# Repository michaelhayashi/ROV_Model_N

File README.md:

ROV_Model_N
===========

Purdue IEEE ROV Team project files

All of the electrical and code files are provided here free of charge for enthusiasts to modify, hack, fix, and do whatever to under OSHW. All files are given without any guarantee.

If anyone does have a cool idea about how to reuse/repurpose any of this hardware, or notices any glaring issues with it, let us know at purduerov@gmail.com

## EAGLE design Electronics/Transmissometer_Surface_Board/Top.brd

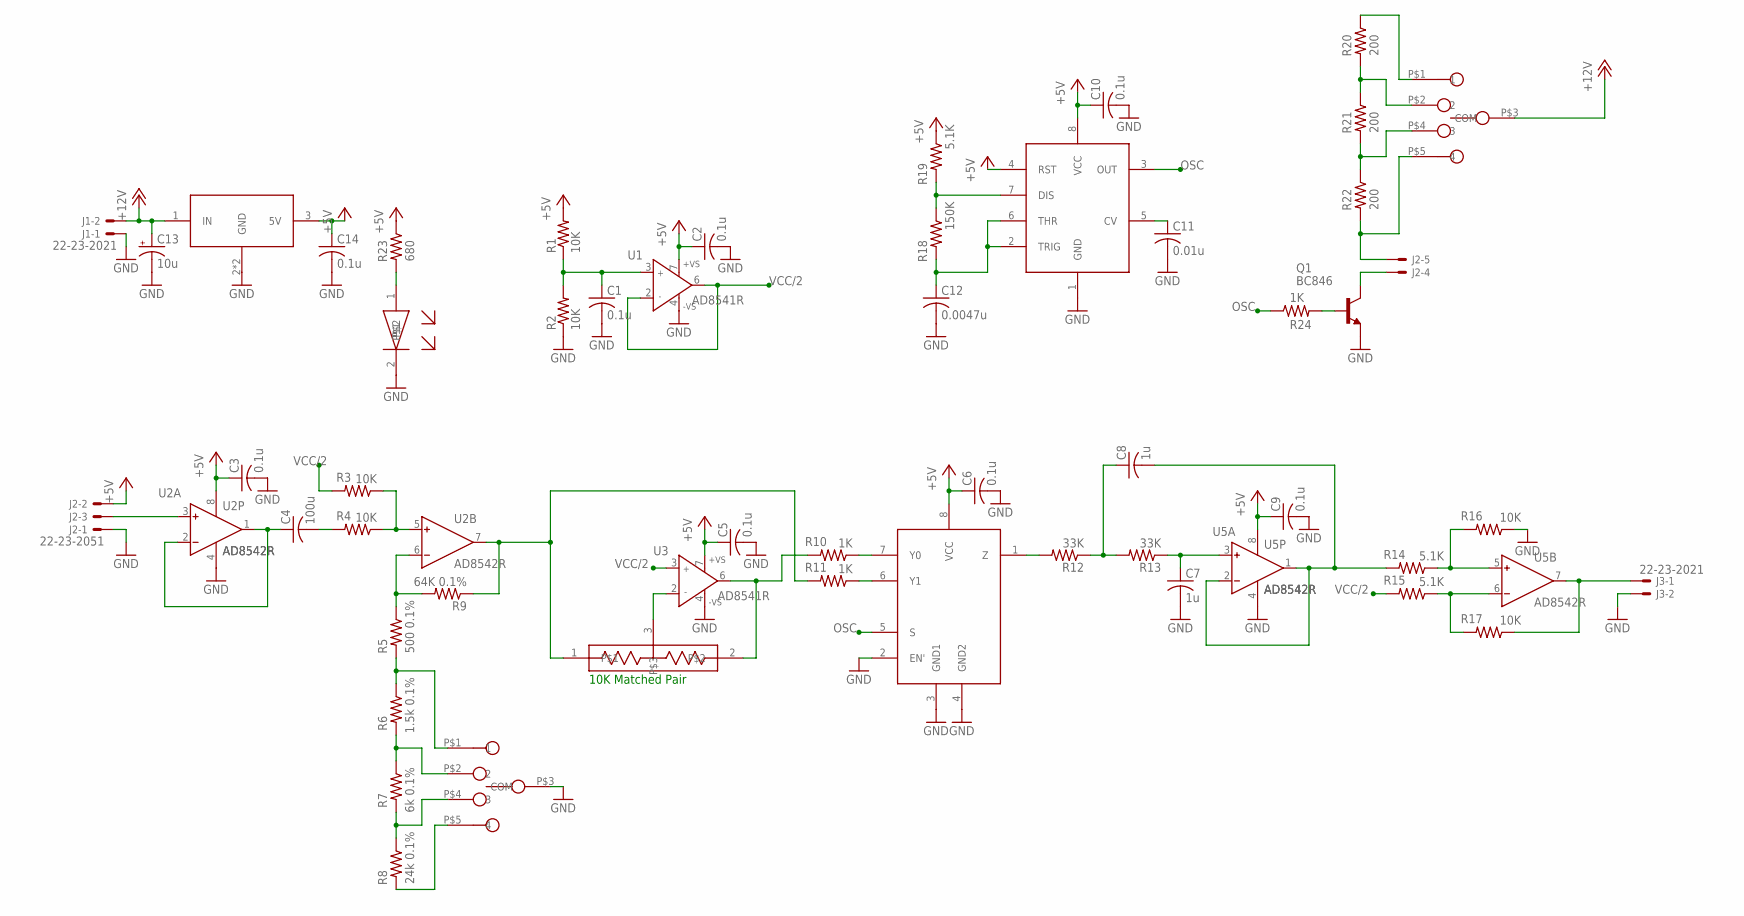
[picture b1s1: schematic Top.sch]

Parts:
C1, C2, C3, C5, C6, C9, C10, C14: 0.1u; C0805
C4: 100u; C1206
C7, C8: 1u; C0805
C11: 0.01u; C0805
C12: 0.0047u; C0805
C13: 10u; E2-5
D1: LGN971; R1206
J1, J3: 22-23-2021
J2: 22-23-2051
Q1: BC846; SOT23
R1, R2, R3, R4, R16, R17: 10K; R0805
R5: 500 0.1%; R0805
R6: 1.5k 0.1%; R0805
R7: 6k 0.1%; R0805
R8: 24k 0.1%; R0805
R9: 64K 0.1%; R0805
R10, R11, R24: 1K; R0805
R12, R13: 33K; R0805
R14, R15, R19: 5.1K; R0805
R18: 150K; R0805
R20, R21, R22: 200; R0805
R23: 680; R0805
RN1: MPMT2002; SOT23
SW1, SW2: STS1400; 2-3SW
U1, U3: AD8541R; SO8
U2, U5: AD8542R; SO8
U4: 74LVC1G53; SOP08
U6: NA555; SO8
U7: UA78M05CDCYR; SOT223-W

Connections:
+5V: C2.1, C3.1, C5.1, C6.1, C9.1, C10.1, C14.1, J2.2, R1.2, R19.1, R23.1, U1.7 (+VS), U2.8 (V+), U3.7 (+VS), U4.8 (VCC), U5.8 (V+), U6.4 (RST), U6.8 (VCC), U7.3 (5V)
+12V: C13.+, J1.2, SW2.P$3 (COM), U7.1 (IN)
GND: C1.2, C2.2, C3.2, C5.2, C6.2, C7.2, C9.2, C10.2, C11.2, C12.2, C13.-, C14.2, D1.2, J1.1, J2.1, J3.2, Q1.2 (E), R2.1, R16.1, SW1.P$3 (COM), U1.4 (-VS), U2.4 (V-), U3.4 (-VS), U4.2 (EN'), U4.3 (GND1), U4.4 (GND2), U5.4 (V-), U6.1 (GND), U7.2 (GND), U7.4 (GND)
unnamed: C1.1, R1.1, R2.2, U1.3 (IN+)
unnamed: C4.1, U2.1 (OUT), U2.2 (IN-)
unnamed: C4.2, R4.2
unnamed: R3.1, R4.1, U2.5 (IN+)
unnamed: R5.1, R9.2, U2.6 (IN-)
unnamed: R9.1, R11.2, RN1.1, U2.7 (OUT)
unnamed: R7.2, R8.1, SW1.P$4 (3)
unnamed: R6.2, R7.1, SW1.P$2 (2)
unnamed: R5.2, R6.1, SW1.P$1 (1)
unnamed: RN1.3, U3.2 (IN-)
unnamed: R10.2, RN1.2, U3.6 (OUT)
unnamed: R10.1, U4.7 (Y0)
unnamed: R11.1, U4.6 (Y1)
unnamed: C8.1, R12.1, R13.2
unnamed: C7.1, R13.1, U5.3 (IN+)
unnamed: C8.2, R14.2, U5.1 (OUT), U5.2 (IN-)
unnamed: R18.1, R19.2, U6.7 (DIS)
unnamed: R14.1, R16.2, U5.5 (IN+)
unnamed: R15.1, R17.2, U5.6 (IN-)
unnamed: J3.1, R17.1, U5.7 (OUT)
unnamed: D1.1, R23.2
unnamed: R12.2, U4.1 (Z)
unnamed: C12.1, R18.2, U6.2 (TRIG), U6.6 (THR)
unnamed: Q1.1 (B), R24.2
unnamed: J2.5, R22.2, SW2.P$5 (4)
unnamed: C11.1, U6.5 (CV)
unnamed: J2.4, Q1.3 (C)
unnamed: J2.3, U2.3 (IN+)
unnamed: R8.2, SW1.P$5 (4)
unnamed: R21.2, R22.1, SW2.P$4 (3)
unnamed: R20.2, R21.1, SW2.P$2 (2)
unnamed: R20.1, SW2.P$1 (1)
OSC: R24.1, U4.5 (S), U6.3 (OUT)
VCC/2: R3.2, R15.2, U1.2 (IN-), U1.6 (OUT), U3.3 (IN+)

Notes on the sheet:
10K Matched Pair

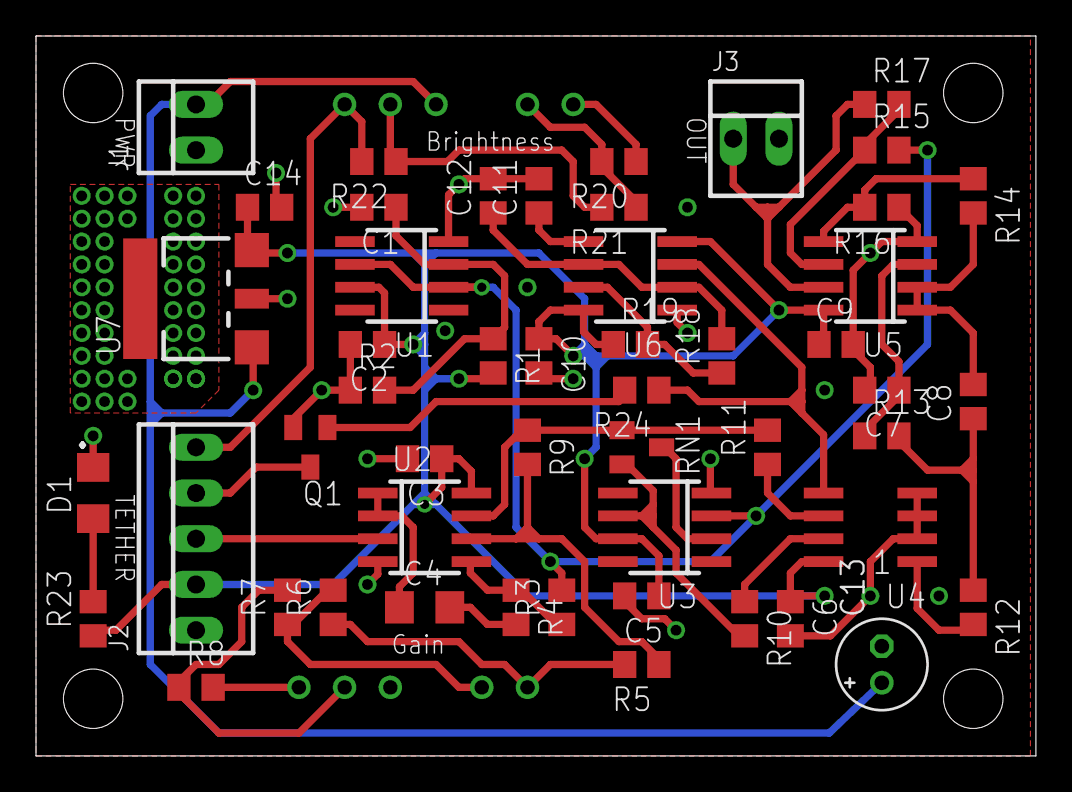
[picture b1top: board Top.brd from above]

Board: 2 copper layers, 55.5 x 40.0 mm, 57 parts (0 on the bottom side), 37 nets.

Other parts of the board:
U$1, U$2, U$3, U$4: STAND-OFF

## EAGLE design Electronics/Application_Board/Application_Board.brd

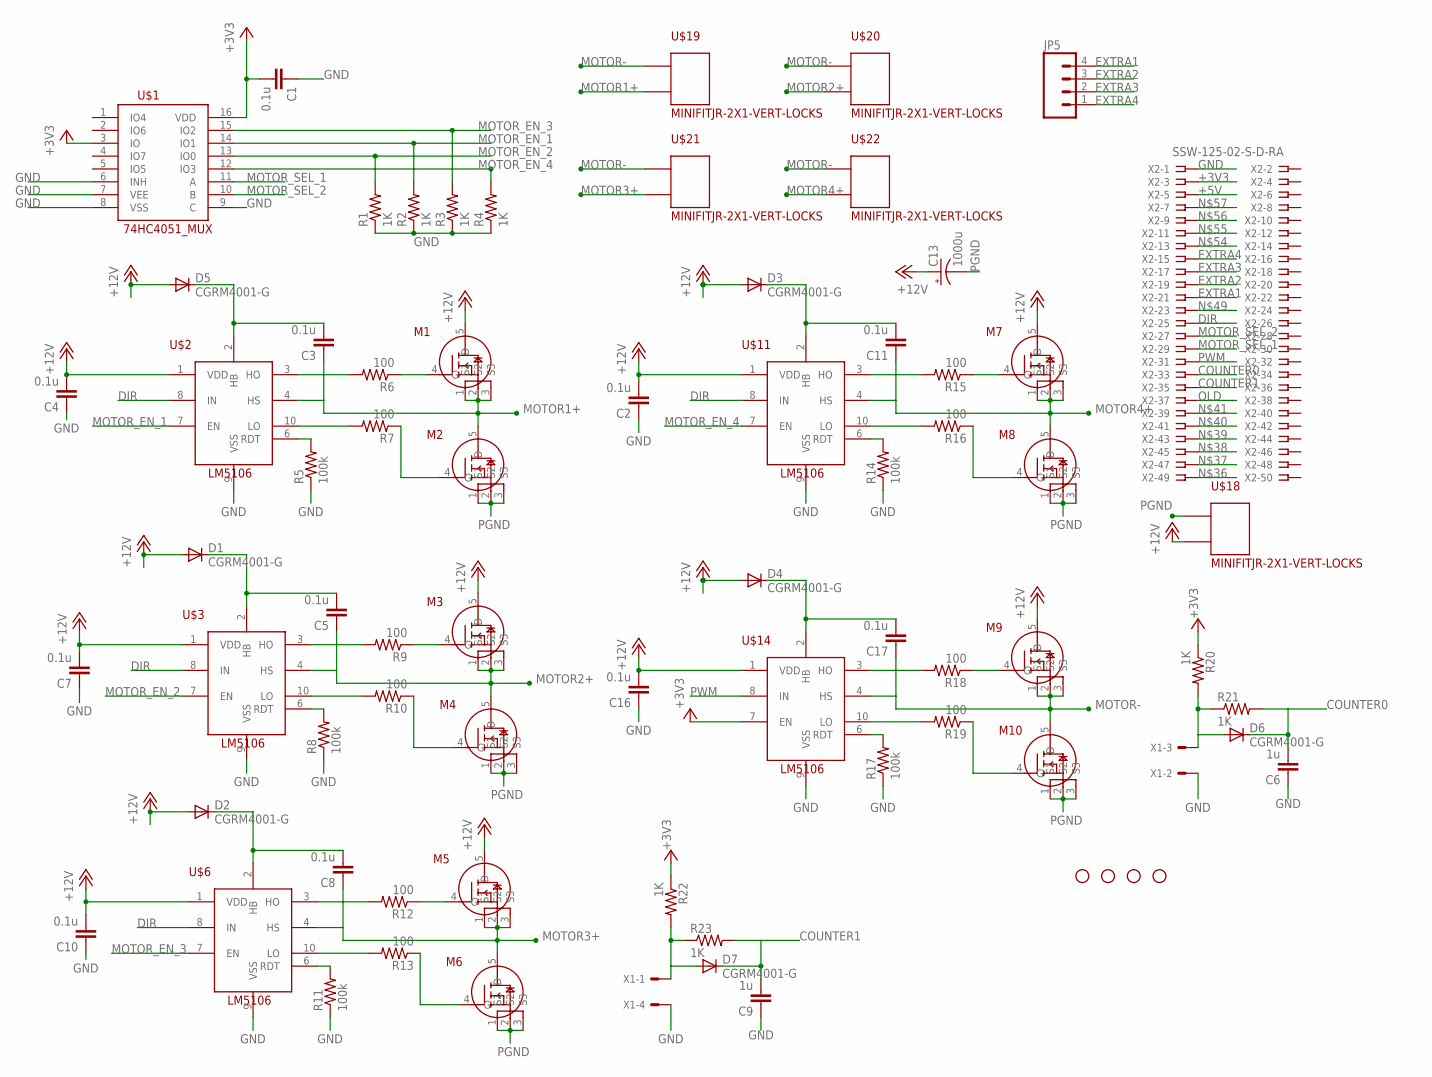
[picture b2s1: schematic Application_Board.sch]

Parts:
C1, C2, C3, C4, C5, C7, C8, C10, C11, C16, C17: 0.1u; 0805
C6, C9: 1u; 0805
C13: 1000u; UD-18X19,1_NICHICON
D1, D2, D3, D4, D5, D6, D7: CGRM4001-G; SOD-123_MINI-SMA
JP1, JP2, JP3, JP4: STAND-OFF
JP5: M041X04_NO_SILK; 1X04_NO_SILK
M1, M2, M3, M4, M5, M6, M7, M8, M9, M10: M; TO127P600X120-5N
R1, R2, R3, R4, R20, R21, R22, R23: 1K; R0805
R5, R8, R11, R14, R17: 100k; R0805
R6, R7, R9, R10, R12, R13, R15, R16, R18, R19: 100; R0805
U$1: 74HC4051_MUX; SO16
U$2, U$3, U$6, U$11, U$14: LM5106MMSMD-MSOP; 10-MSOP
U$18, U$19, U$20, U$21, U$22: MINIFITJR-2X1-VERT-LOCKS; 5566-02A2
X1: KK-156-4
X2: SSW-125-02-S-D-RA; TSW-125-02-S-D-RA

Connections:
+3V3: C1.2, R20.1, R22.1, U$1.3 (IO), U$1.16 (VDD), U$14.7 (EN), X2.3
+5V: X2.5
+12V: C2.2, C4.2, C7.2, C10.2, C13.+, C16.2, D1.A, D2.A, D3.A, D4.A, D5.A, M1.5 (D), M3.5 (D), M5.5 (D), M7.5 (D), M9.5 (D), U$2.1 (VDD), U$3.1 (VDD), U$6.1 (VDD), U$11.1 (VDD), U$14.1 (VDD), U$18.P$2
COUNTER0: C6.2, D6.C, R21.2, X2.33
COUNTER1: C9.2, D7.C, R23.2, X2.35
DIR: U$2.8 (IN), U$3.8 (IN), U$6.8 (IN), U$11.8 (IN), X2.25
EXTRA1: JP5.4, X2.21
EXTRA2: JP5.3, X2.19
EXTRA3: JP5.2, X2.17
EXTRA4: JP5.1, X2.15
GND: C1.1, C2.1, C4.1, C6.1, C7.1, C9.1, C10.1, C16.1, R1.1, R2.1, R3.1, R4.1, R5.1, R8.1, R11.1, R14.1, R17.1, U$1.6 (INH), U$1.7 (VEE), U$1.8 (VSS), U$1.9 (C), U$2.9 (VSS), U$3.9 (VSS), U$6.9 (VSS), U$11.9 (VSS), U$14.9 (VSS), X1.2, X1.4, X2.1
MOTOR1+: C3.1, M1.1 (S1), M1.2 (S2), M1.3 (S3), M2.5 (D), U$2.4 (HS), U$19.P$2
MOTOR2+: C5.1, M3.1 (S1), M3.2 (S2), M3.3 (S3), M4.5 (D), U$3.4 (HS), U$20.P$2
MOTOR3+: C8.1, M5.1 (S1), M5.2 (S2), M5.3 (S3), M6.5 (D), U$6.4 (HS), U$21.P$2
MOTOR4+: C11.1, M7.1 (S1), M7.2 (S2), M7.3 (S3), M8.5 (D), U$11.4 (HS), U$22.P$2
MOTOR-: C17.1, M9.1 (S1), M9.2 (S2), M9.3 (S3), M10.5 (D), U$14.4 (HS), U$19.P$1, U$20.P$1, U$21.P$1, U$22.P$1
MOTOR_EN_1: R2.2, U$1.14 (IO1), U$2.7 (EN)
MOTOR_EN_2: R1.2, U$1.13 (IO0), U$3.7 (EN)
MOTOR_EN_3: R3.2, U$1.15 (IO2), U$6.7 (EN)
MOTOR_EN_4: R4.2, U$1.12 (IO3), U$11.7 (EN)
MOTOR_SEL_1: U$1.11 (A), X2.29
MOTOR_SEL_2: U$1.10 (B), X2.27
unnamed: C3.2, D5.C, U$2.2 (HB)
unnamed: R9.2, U$3.3 (HO)
unnamed: R10.2, U$3.10 (LO)
unnamed: M1.4 (G), R6.1
unnamed: R5.2, U$2.6 (RDT)
unnamed: C5.2, D1.C, U$3.2 (HB)
unnamed: R8.2, U$3.6 (RDT)
unnamed: M2.4 (G), R7.1
unnamed: M3.4 (G), R9.1
unnamed: M4.4 (G), R10.1
unnamed: R12.2, U$6.3 (HO)
unnamed: R13.2, U$6.10 (LO)
unnamed: C8.2, D2.C, U$6.2 (HB)
unnamed: R11.2, U$6.6 (RDT)
unnamed: M5.4 (G), R12.1
unnamed: M6.4 (G), R13.1
unnamed: R15.2, U$11.3 (HO)
unnamed: R16.2, U$11.10 (LO)
unnamed: C11.2, D3.C, U$11.2 (HB)
unnamed: R14.2, U$11.6 (RDT)
unnamed: M7.4 (G), R15.1
unnamed: M8.4 (G), R16.1
unnamed: R18.2, U$14.3 (HO)
unnamed: R19.2, U$14.10 (LO)
unnamed: C17.2, D4.C, U$14.2 (HB)
unnamed: R17.2, U$14.6 (RDT)
unnamed: M9.4 (G), R18.1
unnamed: M10.4 (G), R19.1
unnamed: D7.A, R22.2, R23.1, X1.1
unnamed: D6.A, R20.2, R21.1, X1.3
unnamed: R6.2, U$2.3 (HO)
unnamed: R7.2, U$2.10 (LO)
OLD: X2.37
PGND: C13.-, M2.1 (S1), M2.2 (S2), M2.3 (S3), M4.1 (S1), M4.2 (S2), M4.3 (S3), M6.1 (S1), M6.2 (S2), M6.3 (S3), M8.1 (S1), M8.2 (S2), M8.3 (S3), M10.1 (S1), M10.2 (S2), M10.3 (S3), U$18.P$1
PWM: U$14.8 (IN), X2.31

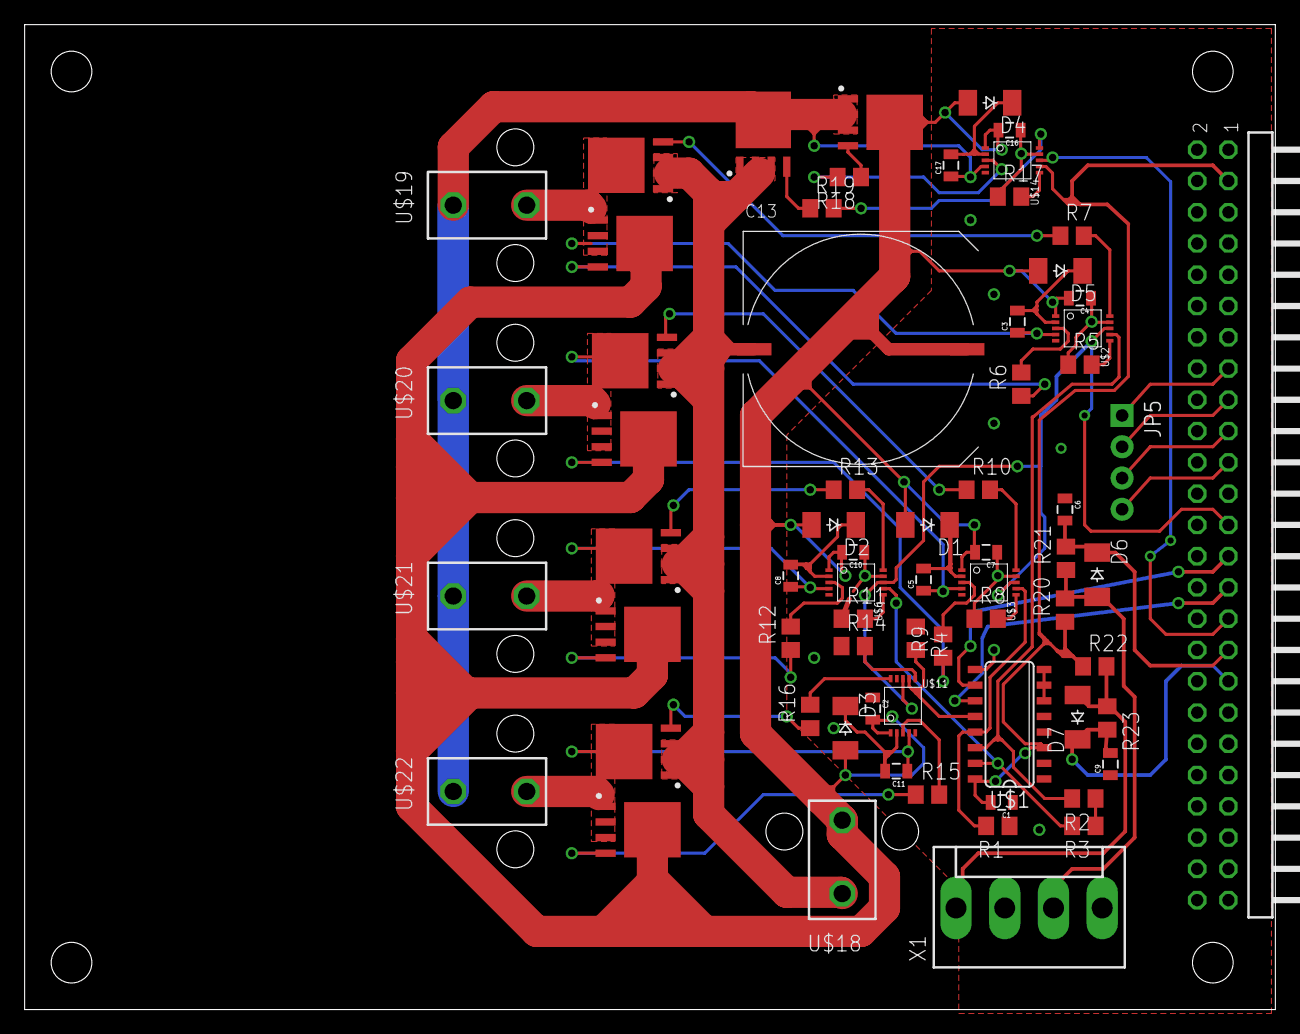
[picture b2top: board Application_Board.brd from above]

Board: 2 copper layers, 101.6 x 80.0 mm, 72 parts (0 on the bottom side), 55 nets.

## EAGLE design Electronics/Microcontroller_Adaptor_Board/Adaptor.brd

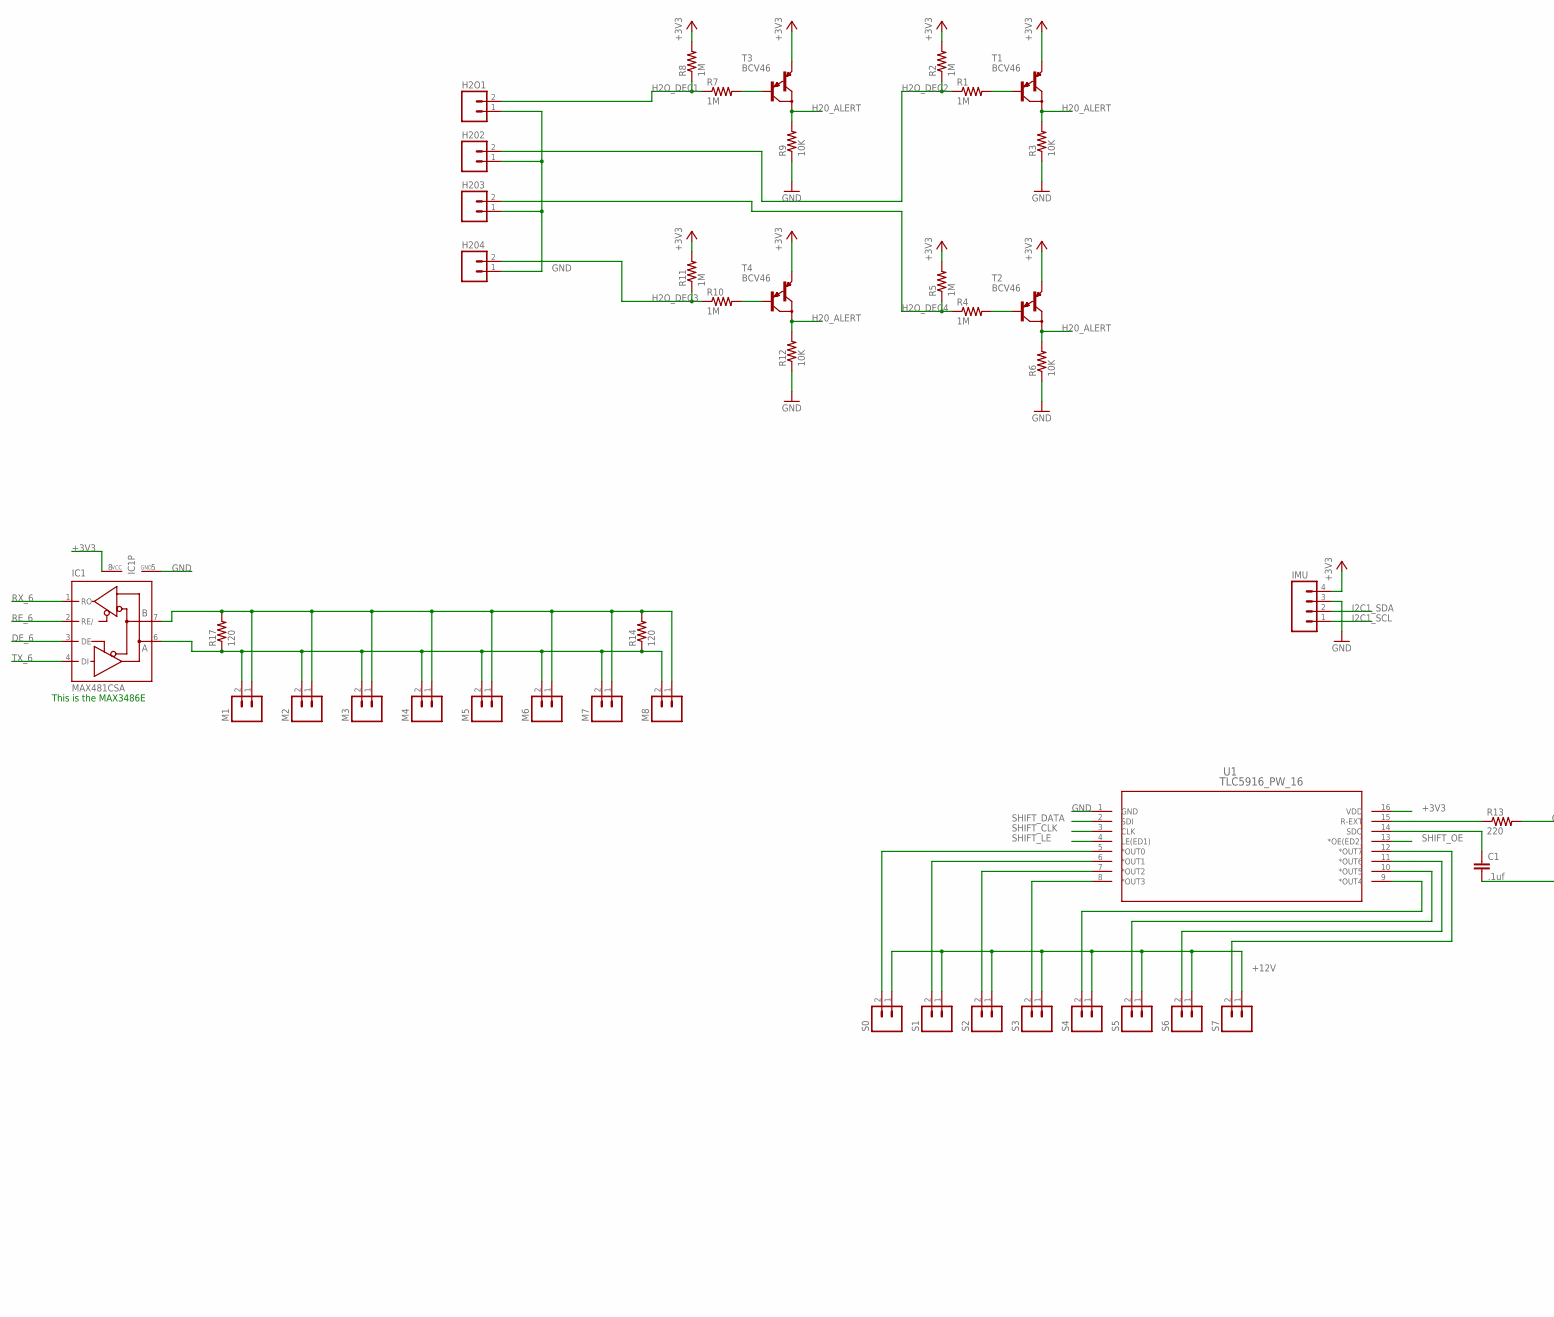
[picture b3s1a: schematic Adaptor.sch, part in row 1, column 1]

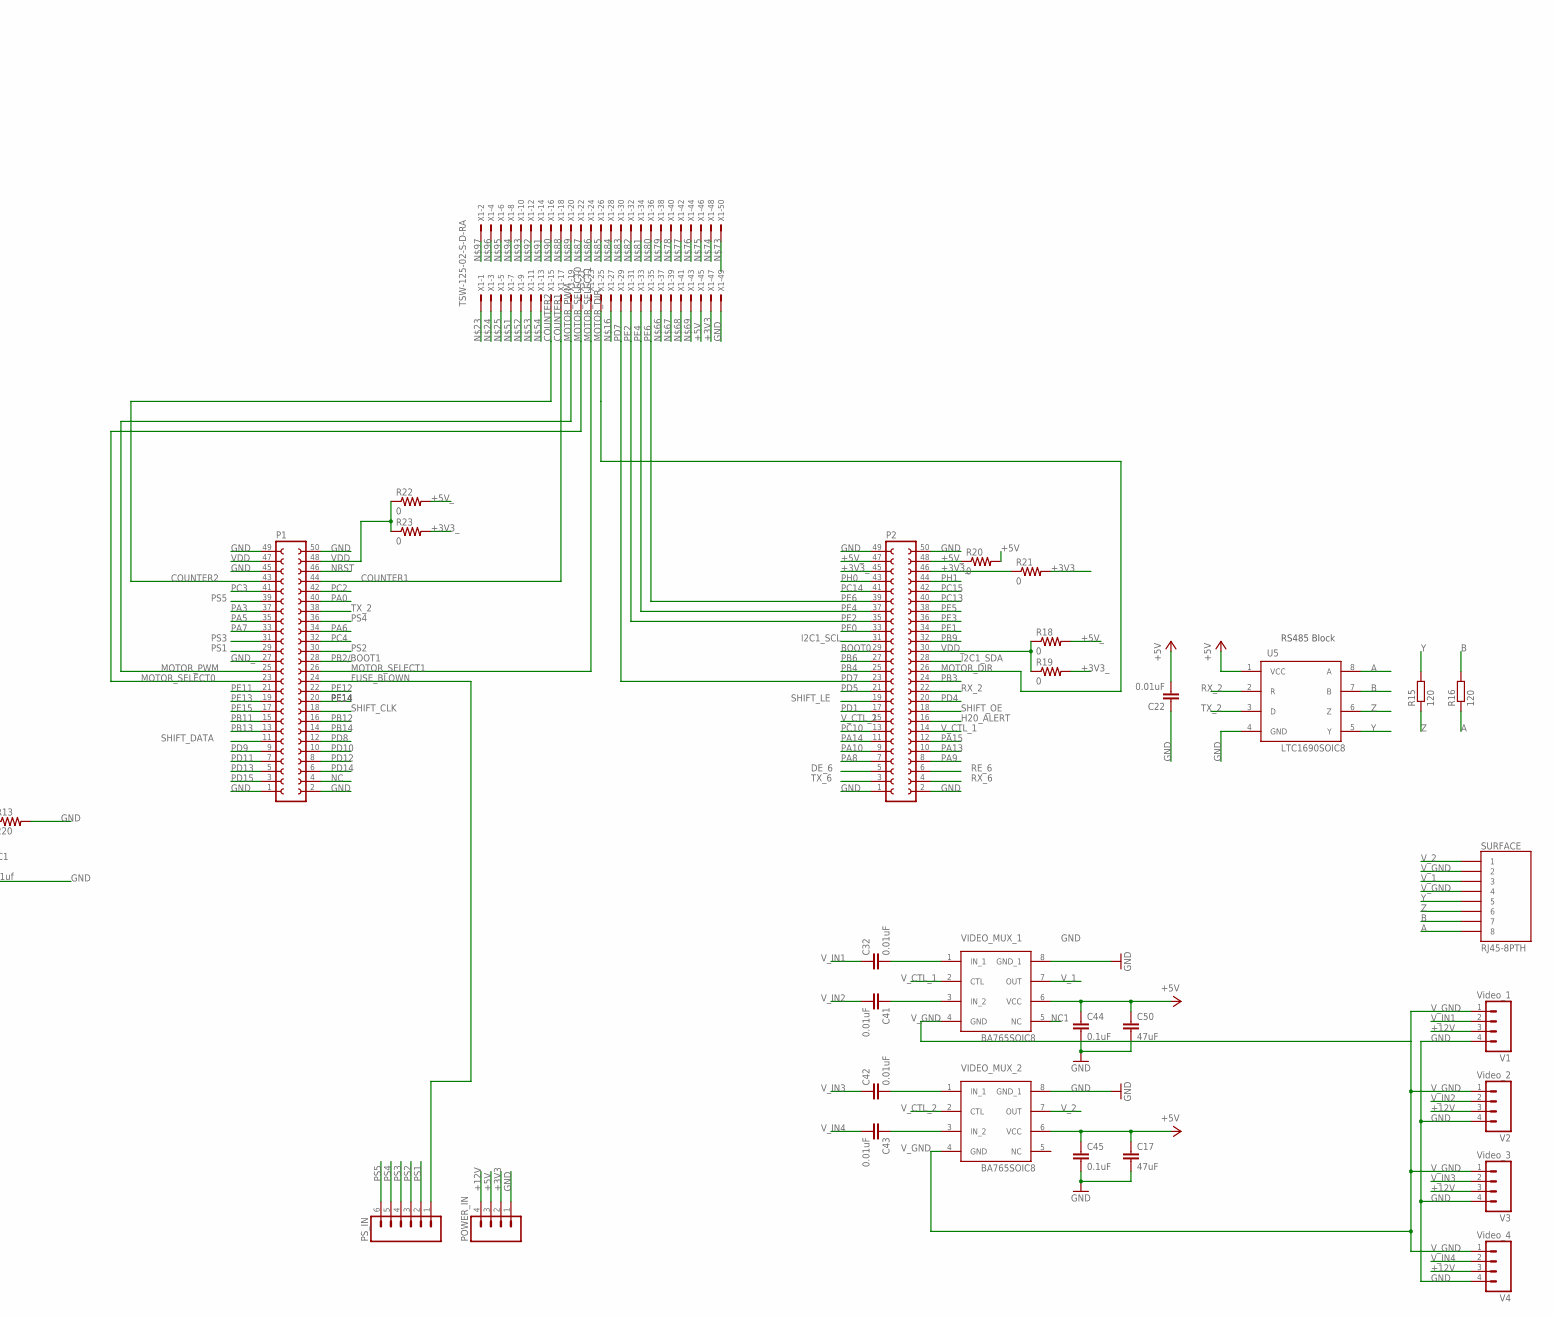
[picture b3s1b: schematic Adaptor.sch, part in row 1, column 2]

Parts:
C1: .1uf; 0805
C17, C50: 47uF; C1206; PARTNO 490-5528-1-ND
C22, C32, C41, C42, C43: 0.01uF; C0603; PARTNO 478-1227-1-ND
C44, C45: 0.1uF; C0603; PARTNO 311-1344-1-ND
H2O1, H202, H203, H204: M02PTH; 1X02
IC1: MAX481CSA; SO08
IMU: M04PTH; 1X04
M1, M2, M3, M4, M5, M6, M7, M8: M02PTH; 1X02
P1, P2: FE25-2
POWER_IN: M04PTH; 1X04
PS_IN: M06SIP; 1X06
R1, R2, R4, R5, R7, R8, R10, R11: 1M; 0805
R3, R6, R9, R12: 10K; 0805
R13: 220; 0805
R14, R17: 120; 0805
R15, R16: 120; R0603
R18, R19, R20, R21, R22, R23: 0; 0805
S0, S1, S2, S3, S4, S5, S6, S7: M02PTH; 1X02
SURFACE: RJ45-8PTH; RJ45-8
T1, T2, T3, T4: BCV46; SOT23-BEC
U1: TLC5916_PW_16; PW16
U5: LTC1690SOIC8; SOIC8
V1: Video_1; 1X04
V2: Video_2; 1X04
V3: Video_3; 1X04
V4: Video_4; 1X04
VIDEO_MUX_1, VIDEO_MUX_2: BA765SOIC8; SOIC8
X1: TSW-125-02-S-D-RA

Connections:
+3V3: IC1.8 (VCC), IMU.4, POWER_IN.2, R2.2, R5.2, R8.2, R11.2, R21.2, T1.E, T2.E, T3.E, T4.E, U1.16 (VDD), X1.47
+3V3_: P2.45, P2.46, R19.2, R21.1, R23.2
+5V: C17.1, C22.2, C44.1, C45.1, C50.1, POWER_IN.3, R20.2, U5.1 (VCC), VIDEO_MUX_1.6 (VCC), VIDEO_MUX_2.6 (VCC), X1.45
+5V_: P2.47, P2.48, R18.2, R20.1, R22.2
+12V: POWER_IN.4, S0.1, S1.1, S2.1, S3.1, S4.1, S5.1, S6.1, S7.1, V1.3, V2.3, V3.3, V4.3
A: R16.1, SURFACE.8, U5.8 (A)
B: R16.2, SURFACE.7, U5.7 (B)
BOOT0: P2.29
COUNTER1: P1.44, X1.17
COUNTER2: P1.43, X1.15
DE_6: IC1.3 (DE), P2.5
FUSE_BLOWN: P1.24, PS_IN.1
GND: C1.2, C17.2, C22.1, C44.2, C45.2, C50.2, H2O1.1, H202.1, H203.1, H204.1, IC1.5 (GND), IMU.3, P1.1, P1.2, P1.45, P1.49, P1.50, P2.1, P2.2, P2.49, P2.50, POWER_IN.1, R3.1, R6.1, R9.1, R12.1, R13.2, U1.1 (GND), U5.4 (GND), V1.4, V2.4, V3.4, V4.4, VIDEO_MUX_1.8 (GND_1), VIDEO_MUX_2.8 (GND_1), X1.49
GND_: P1.27
H2O_DEC1: H2O1.2, R7.1, R8.1
H2O_DEC2: H202.2, R1.1, R2.1
H2O_DEC3: H204.2, R10.1, R11.1
H2O_DEC4: H203.2, R4.1, R5.1
H20_ALERT: P2.16, R3.2, R6.2, R9.2, R12.2, T1.C, T2.C, T3.C, T4.C
I2C1_SCL: IMU.1, P2.31
I2C1_SDA: IMU.2, P2.28
MOTOR_DIR: P2.26, X1.25
MOTOR_PWM: P1.25, X1.19
MOTOR_SELECT0: P1.23, X1.21
MOTOR_SELECT1: P1.26, X1.23
unnamed: R1.2, T1.B
unnamed: R4.2, T2.B
unnamed: R7.2, T3.B
unnamed: R10.2, T4.B
unnamed: IC1.7 (B), M1.1, M2.1, M3.1, M4.1, M5.1, M6.1, M7.1, M8.1, R14.2, R17.2
unnamed: C32.2, VIDEO_MUX_1.1 (IN_1)
unnamed: C41.1, VIDEO_MUX_1.3 (IN_2)
unnamed: S0.2, U1.5 (*OUT0)
unnamed: S1.2, U1.6 (*OUT1)
unnamed: S2.2, U1.7 (*OUT2)
unnamed: S3.2, U1.8 (*OUT3)
unnamed: C42.2, VIDEO_MUX_2.1 (IN_1)
unnamed: R13.1, U1.15 (R-EXT)
unnamed: C1.1, U1.14 (SDO)
unnamed: S7.2, U1.12 (*OUT7)
unnamed: S6.2, U1.11 (*OUT6)
unnamed: S5.2, U1.10 (*OUT5)
unnamed: S4.2, U1.9 (*OUT4)
unnamed: C43.1, VIDEO_MUX_2.3 (IN_2)
unnamed: IC1.6 (A), M1.2, M2.2, M3.2, M4.2, M5.2, M6.2, M7.2, M8.2, R14.1, R17.1
NC: P1.4
NC1: VIDEO_MUX_1.5 (NC)
NRST: P1.46
PA0: P1.40
PA3: P1.37
PA5: P1.35
PA6: P1.34
PA7: P1.33
PA8: P2.7
PA9: P2.8
PA10: P2.9
PA13: P2.10
PA14: P2.11
PA15: P2.12
PB2/BOOT1: P1.28
PB3: P2.24
PB4: P2.25
PB6: P2.27
PB9: P2.32
PB11: P1.15
PB12: P1.16
PB13: P1.13
PB14: P1.14
PC2: P1.42
PC3: P1.41
PC4: P1.32
PC10: P2.13
PC13: P2.40
PC14: P2.41
PC15: P2.42
PD1: P2.17
PD4: P2.20
PD5: P2.21
PD7: P2.23, X1.29
PD8: P1.12
PD9: P1.9
PD10: P1.10
PD11: P1.7
PD12: P1.8
PD13: P1.5
PD14: P1.6
PD15: P1.3
PE0: P2.33
PE1: P2.34
PE2: P2.35, X1.31
PE3: P2.36
PE4: P2.37, X1.33
PE5: P2.38
PE6: P2.39, X1.35
PE11: P1.21
PE12: P1.22
PE13: P1.19
PE14: P1.20
PE15: P1.17
PH0: P2.43
PH1: P2.44
PS1: P1.29, PS_IN.2
PS2: P1.30, PS_IN.3
PS3: P1.31, PS_IN.4
PS4: P1.36, PS_IN.5
PS5: P1.39, PS_IN.6
RE_6: IC1.2 (RE/), P2.6
RX_2: P2.22, U5.2 (R)
RX_6: IC1.1 (RO), P2.4
SHIFT_CLK: P1.18, U1.3 (CLK)
SHIFT_DATA: P1.11, U1.2 (SDI)
SHIFT_LE: P2.19, U1.4 (LE(ED1))
SHIFT_OE: P2.18, U1.13 (*OE(ED2))
TX_2: P1.38, U5.3 (D)
TX_6: IC1.4 (DI), P2.3
VDD: P1.47, P1.48, R22.1, R23.1
VDD_: P2.30, R18.1, R19.1
V_1: SURFACE.3, VIDEO_MUX_1.7 (OUT)
V_2: SURFACE.1, VIDEO_MUX_2.7 (OUT)
V_CTL_1: P2.14, VIDEO_MUX_1.2 (CTL)
V_CTL_2: P2.15, VIDEO_MUX_2.2 (CTL)
V_GND: SURFACE.2, SURFACE.4, V1.1, V2.1, V3.1, V4.1, VIDEO_MUX_1.4 (GND), VIDEO_MUX_2.4 (GND)
V_IN1: C32.1, V1.2
V_IN2: C41.2, V2.2
V_IN3: C42.1, V3.2
V_IN4: C43.2, V4.2
Y: R15.2, SURFACE.5, U5.5 (Y)
Z: R15.1, SURFACE.6, U5.6 (Z)

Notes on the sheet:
RS485 Block
This is the MAX3486E

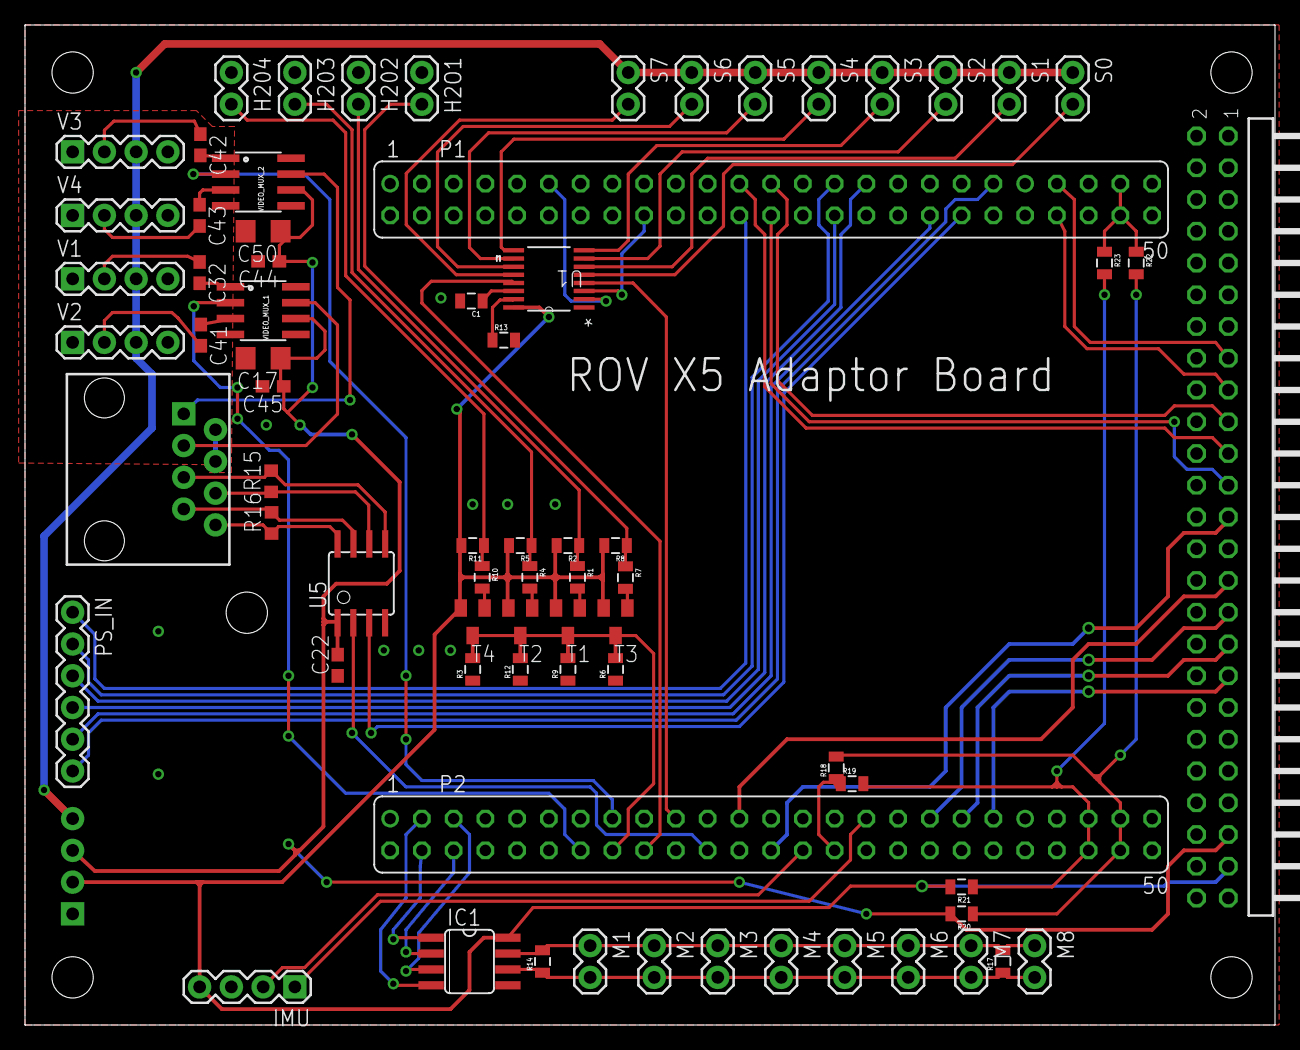
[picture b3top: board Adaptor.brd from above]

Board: 2 copper layers, 100.0 x 80.0 mm, 78 parts (1 on the bottom side), 74 nets.

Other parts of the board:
U$1, U$2, U$3, U$4, U$5: STAND-OFF

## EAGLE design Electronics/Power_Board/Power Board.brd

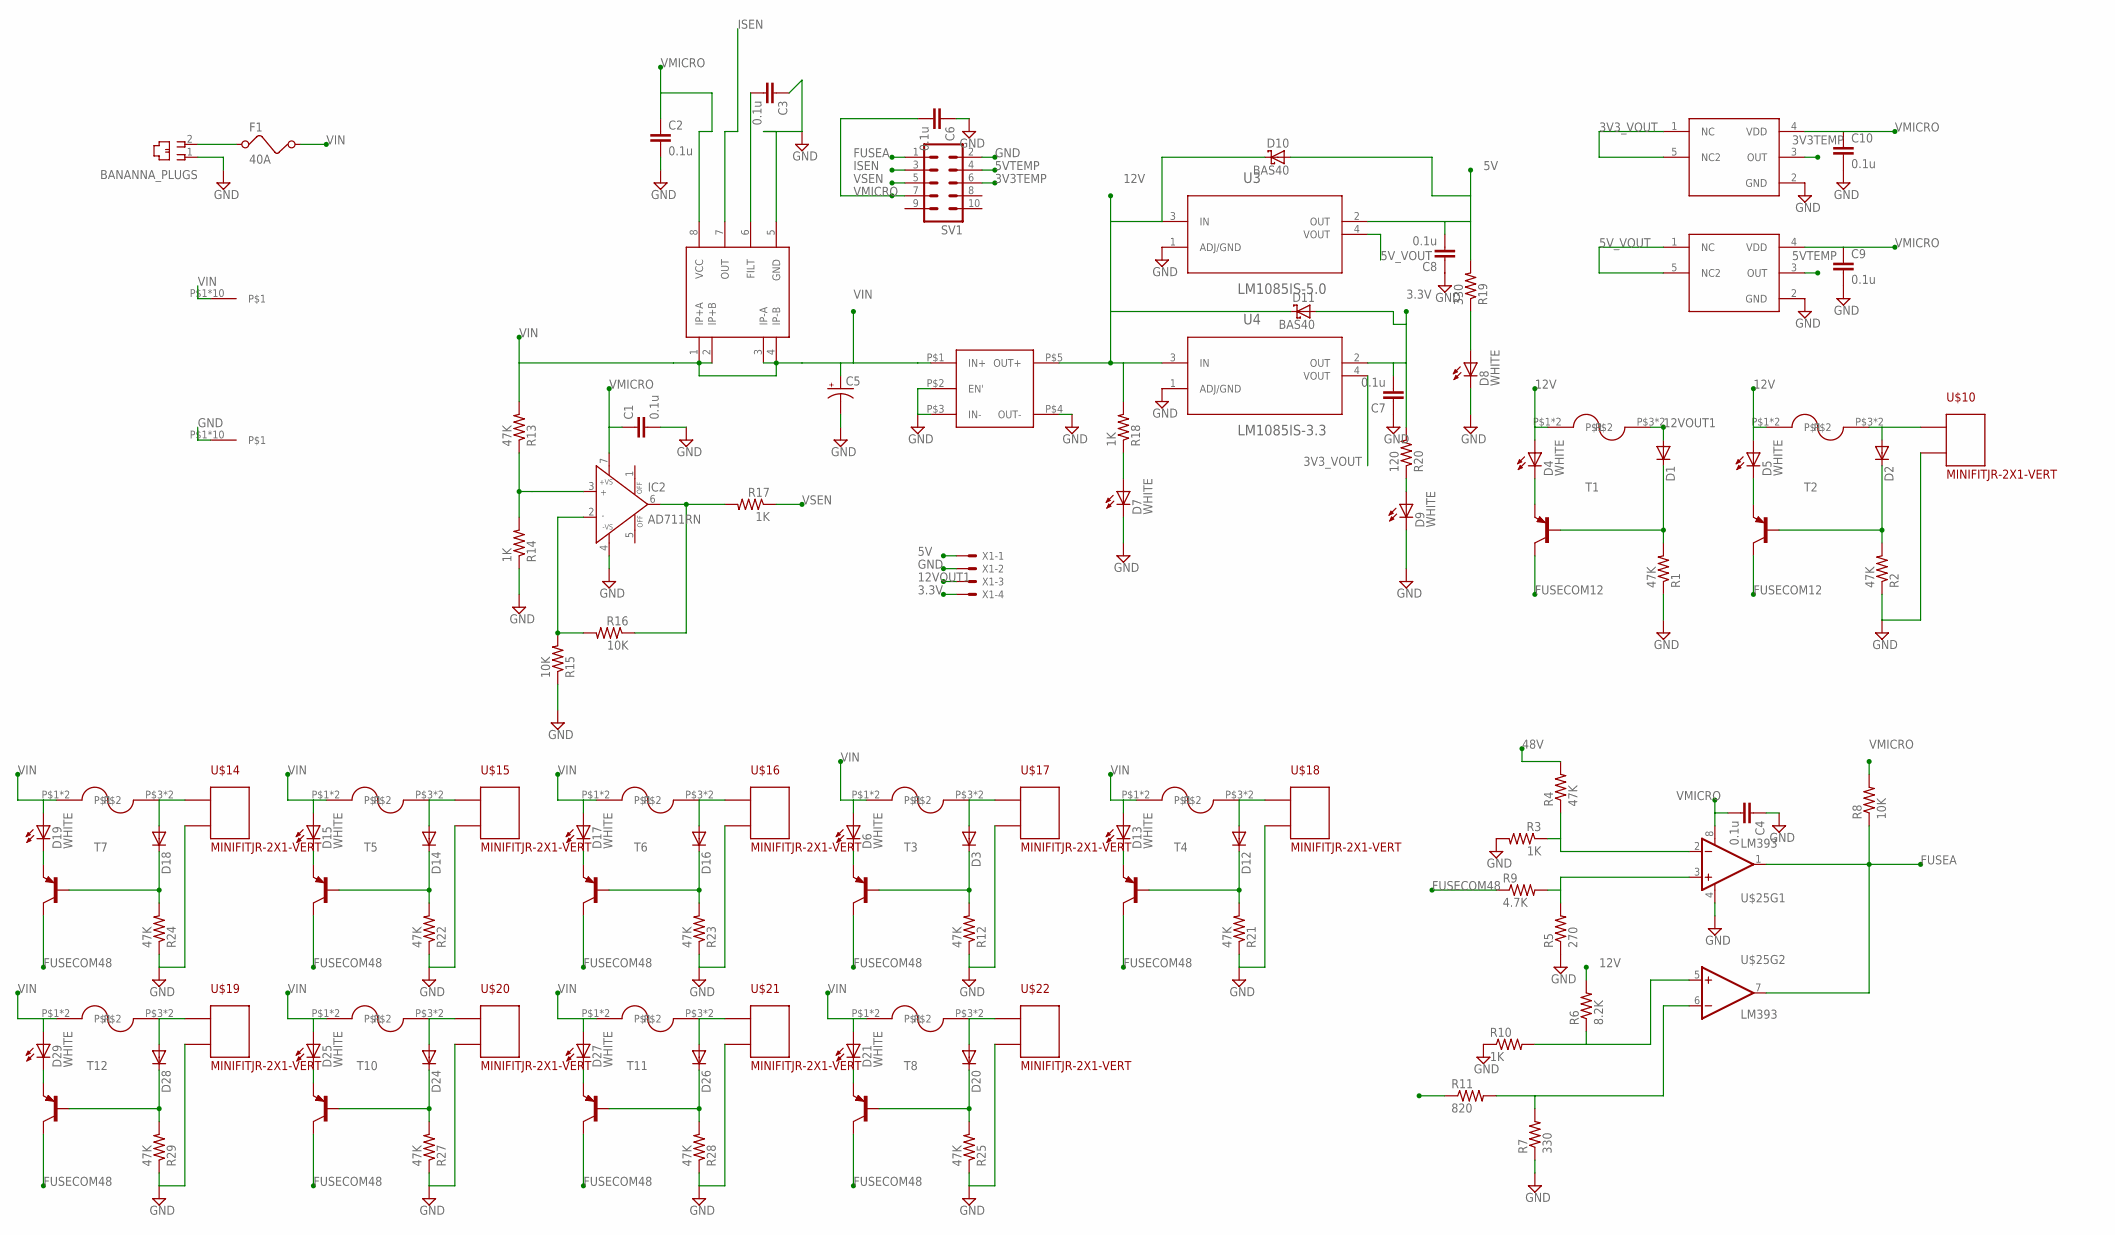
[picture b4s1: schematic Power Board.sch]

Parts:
BANANNA_PLUGS: 520470-4
C1, C2, C3, C4, C6, C7, C8, C9, C10: 0.1u; 0805
C5: CPOL-USE10-30; EB30D
D1, D2, D3, D12, D14, D16, D18, D20, D24, D26, D28: DIODEHV; DIODE-HV
D4, D5, D6, D7, D8, D9, D13, D15, D17, D19, D21, D25, D27, D29: WHITE; LED-1206
D10, D11: BAS40; SOT23
F1: 40A; FUSE
IC2: AD711RN; SO8
R1, R2, R4, R12, R13, R21, R22, R23, R24, R25, R27, R28, R29: 47K; 0805
R3, R10, R14, R17, R18: 1K; 0805
R5: 270; 0805
R6: 8.2K; 0805
R7, R19: 330; 0805
R8, R15, R16: 10K; 0805
R9: 4.7K; 0805
R11: 820; 0805
R20: 120; 0805
SV1: MA05-2
T1, T2, T3, T4, T5, T6, T7, T8, T10, T11, T12: BC856BLT1-PNP-SOT23-BEC; SOT23-BEC
U3: LM1085IS-5.0; TO254P1435X457-3N
U4: LM1085IS-3.3; TO254P1435X457-3N
U$1: SQE48T20120; BRICK
U$2, U$3, U$4, U$5, U$6, U$7, U$8, U$9, U$11, U$12, U$13: FUSEHOLDER3557-2
U$10, U$14, U$15, U$16, U$17, U$18, U$19, U$20, U$21, U$22: MINIFITJR-2X1-VERT; 5566-02B
U$25: LM393; SO08
U$26, U$27: MCP9700T; SOT353
U$30, U$31: SCREW_TERM; TERMINAL
U$32: ACS713; SOP08
X1: KK-156-4

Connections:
3.3V: C7.2, D11.1 (A), R20.2, U4.2 (OUT), X1.4
3V3TEMP: SV1.6, U$27.3 (OUT)
3V3_VOUT: U4.4 (VOUT), U$27.1 (NC), U$27.5 (NC2)
5V: C8.2, D10.1 (A), R19.2, U3.2 (OUT), X1.1
5VTEMP: SV1.4, U$26.3 (OUT)
5V_VOUT: U3.4 (VOUT), U$26.1 (NC), U$26.5 (NC2)
12V: D4.A, D5.A, D10.3 (C), D11.3 (C), R6.2, R18.2, U3.3 (IN), U4.3 (IN), U$1.P$5 (OUT+), U$3.P$1, U$3.P$2, U$4.P$1, U$4.P$2
12VOUT1: D1.A, U$4.P$3, U$4.P$4, X1.3
48V: R4.2
FUSEA: R8.1, SV1.1, U$25.1 (OUT), U$25.7 (OUT)
FUSECOM12: R11.1, T1.C, T2.C
FUSECOM48: R9.1, T3.C, T4.C, T5.C, T6.C, T7.C, T8.C, T10.C, T11.C, T12.C
GND: BANANNA_PLUGS.1, C1.2, C2.2, C3.1, C4.1, C5.-, C6.1, C7.1, C8.1, C9.2, C10.2, D7.C, D8.C, D9.C, IC2.4 (-VS), R1.1, R2.1, R3.2, R5.1, R7.1, R10.1, R12.1, R14.1, R15.1, R21.1, R22.1, R23.1, R24.1, R25.1, R27.1, R28.1, R29.1, SV1.2, U3.1 (ADJ/GND), U4.1 (ADJ/GND), U$1.P$2 (EN'), U$1.P$3 (IN-), U$1.P$4 (OUT-), U$10.P$2, U$14.P$2, U$15.P$2, U$16.P$2, U$17.P$2, U$18.P$2, U$19.P$2, U$20.P$2, U$21.P$2, U$22.P$2, U$25.4 (V-), U$26.2 (GND), U$27.2 (GND), U$31.P$1, U$31.P$2, U$31.P$3, U$31.P$4, U$31.P$5, U$31.P$6, U$31.P$7, U$31.P$8, U$31.P$9, U$31.P$10, U$32.5 (GND), X1.2
ISEN: SV1.3, U$32.7 (OUT)
unnamed: R3.1, R4.1, U$25.2 (-IN)
unnamed: D2.A, U$3.P$3, U$3.P$4, U$10.P$1
unnamed: R5.2, R9.2, U$25.3 (+IN)
unnamed: R6.1, R10.2, U$25.5 (+IN)
unnamed: R7.2, R11.2, U$25.6 (-IN)
unnamed: D2.C, R2.2, T2.B
unnamed: D5.C, T2.E
unnamed: D3.A, U$2.P$3, U$2.P$4, U$17.P$1
unnamed: D3.C, R12.2, T3.B
unnamed: D6.C, T3.E
unnamed: D1.C, R1.2, T1.B
unnamed: D4.C, T1.E
unnamed: C3.2, U$32.6 (FILT)
unnamed: IC2.3 (IN+), R13.1, R14.2
unnamed: IC2.2 (IN-), R15.2, R16.2
unnamed: IC2.6 (OUT), R16.1, R17.2
unnamed: D7.A, R18.1
unnamed: D8.A, R19.1
unnamed: D9.A, R20.1
unnamed: D12.C, R21.2, T4.B
unnamed: D13.C, T4.E
unnamed: BANANNA_PLUGS.2, F1.1
unnamed: D12.A, U$5.P$3, U$5.P$4, U$18.P$1
unnamed: D14.C, R22.2, T5.B
unnamed: D15.C, T5.E
unnamed: D14.A, U$6.P$3, U$6.P$4, U$15.P$1
unnamed: D16.C, R23.2, T6.B
unnamed: D17.C, T6.E
unnamed: D16.A, U$7.P$3, U$7.P$4, U$16.P$1
unnamed: D18.C, R24.2, T7.B
unnamed: D19.C, T7.E
unnamed: D18.A, U$8.P$3, U$8.P$4, U$14.P$1
unnamed: D20.C, R25.2, T8.B
unnamed: D21.C, T8.E
unnamed: D20.A, U$9.P$3, U$9.P$4, U$22.P$1
unnamed: D24.C, R27.2, T10.B
unnamed: D25.C, T10.E
unnamed: D24.A, U$11.P$3, U$11.P$4, U$20.P$1
unnamed: D26.C, R28.2, T11.B
unnamed: D27.C, T11.E
unnamed: D26.A, U$12.P$3, U$12.P$4, U$21.P$1
unnamed: D28.C, R29.2, T12.B
unnamed: D29.C, T12.E
unnamed: D28.A, U$13.P$3, U$13.P$4, U$19.P$1
VIN: C5.+, D6.A, D13.A, D15.A, D17.A, D19.A, D21.A, D25.A, D27.A, D29.A, F1.2, R13.2, U$1.P$1 (IN+), U$2.P$1, U$2.P$2, U$5.P$1, U$5.P$2, U$6.P$1, U$6.P$2, U$7.P$1, U$7.P$2, U$8.P$1, U$8.P$2, U$9.P$1, U$9.P$2, U$11.P$1, U$11.P$2, U$12.P$1, U$12.P$2, U$13.P$1, U$13.P$2, U$30.P$1, U$30.P$2, U$30.P$3, U$30.P$4, U$30.P$5, U$30.P$6, U$30.P$7, U$30.P$8, U$30.P$9, U$30.P$10, U$32.1 (IP+A), U$32.2 (IP+B), U$32.3 (IP-A), U$32.4 (IP-B)
VMICRO: C1.1, C2.1, C4.2, C6.2, C9.1, C10.1, IC2.7 (+VS), R8.2, SV1.7, U$25.8 (V+), U$26.4 (VDD), U$27.4 (VDD), U$32.8 (VCC)
VSEN: R17.1, SV1.5

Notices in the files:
parts and their libraries:
SparkFun-AnalogIC: Licensing: CC v3.0 Share-Alike You are welcome to use this library for commercial purposes.
